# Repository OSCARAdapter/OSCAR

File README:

OSCAR
=====
A Retina screen controlling interface.

Getting Started
---------------
1) Clone this repository
2) make && make upload
3) There is no step 3

Licensing
---------
The software is licensed under the BSD 3-Clause License (check COPYING).
The hardware is licensed under CC-BY-SA.

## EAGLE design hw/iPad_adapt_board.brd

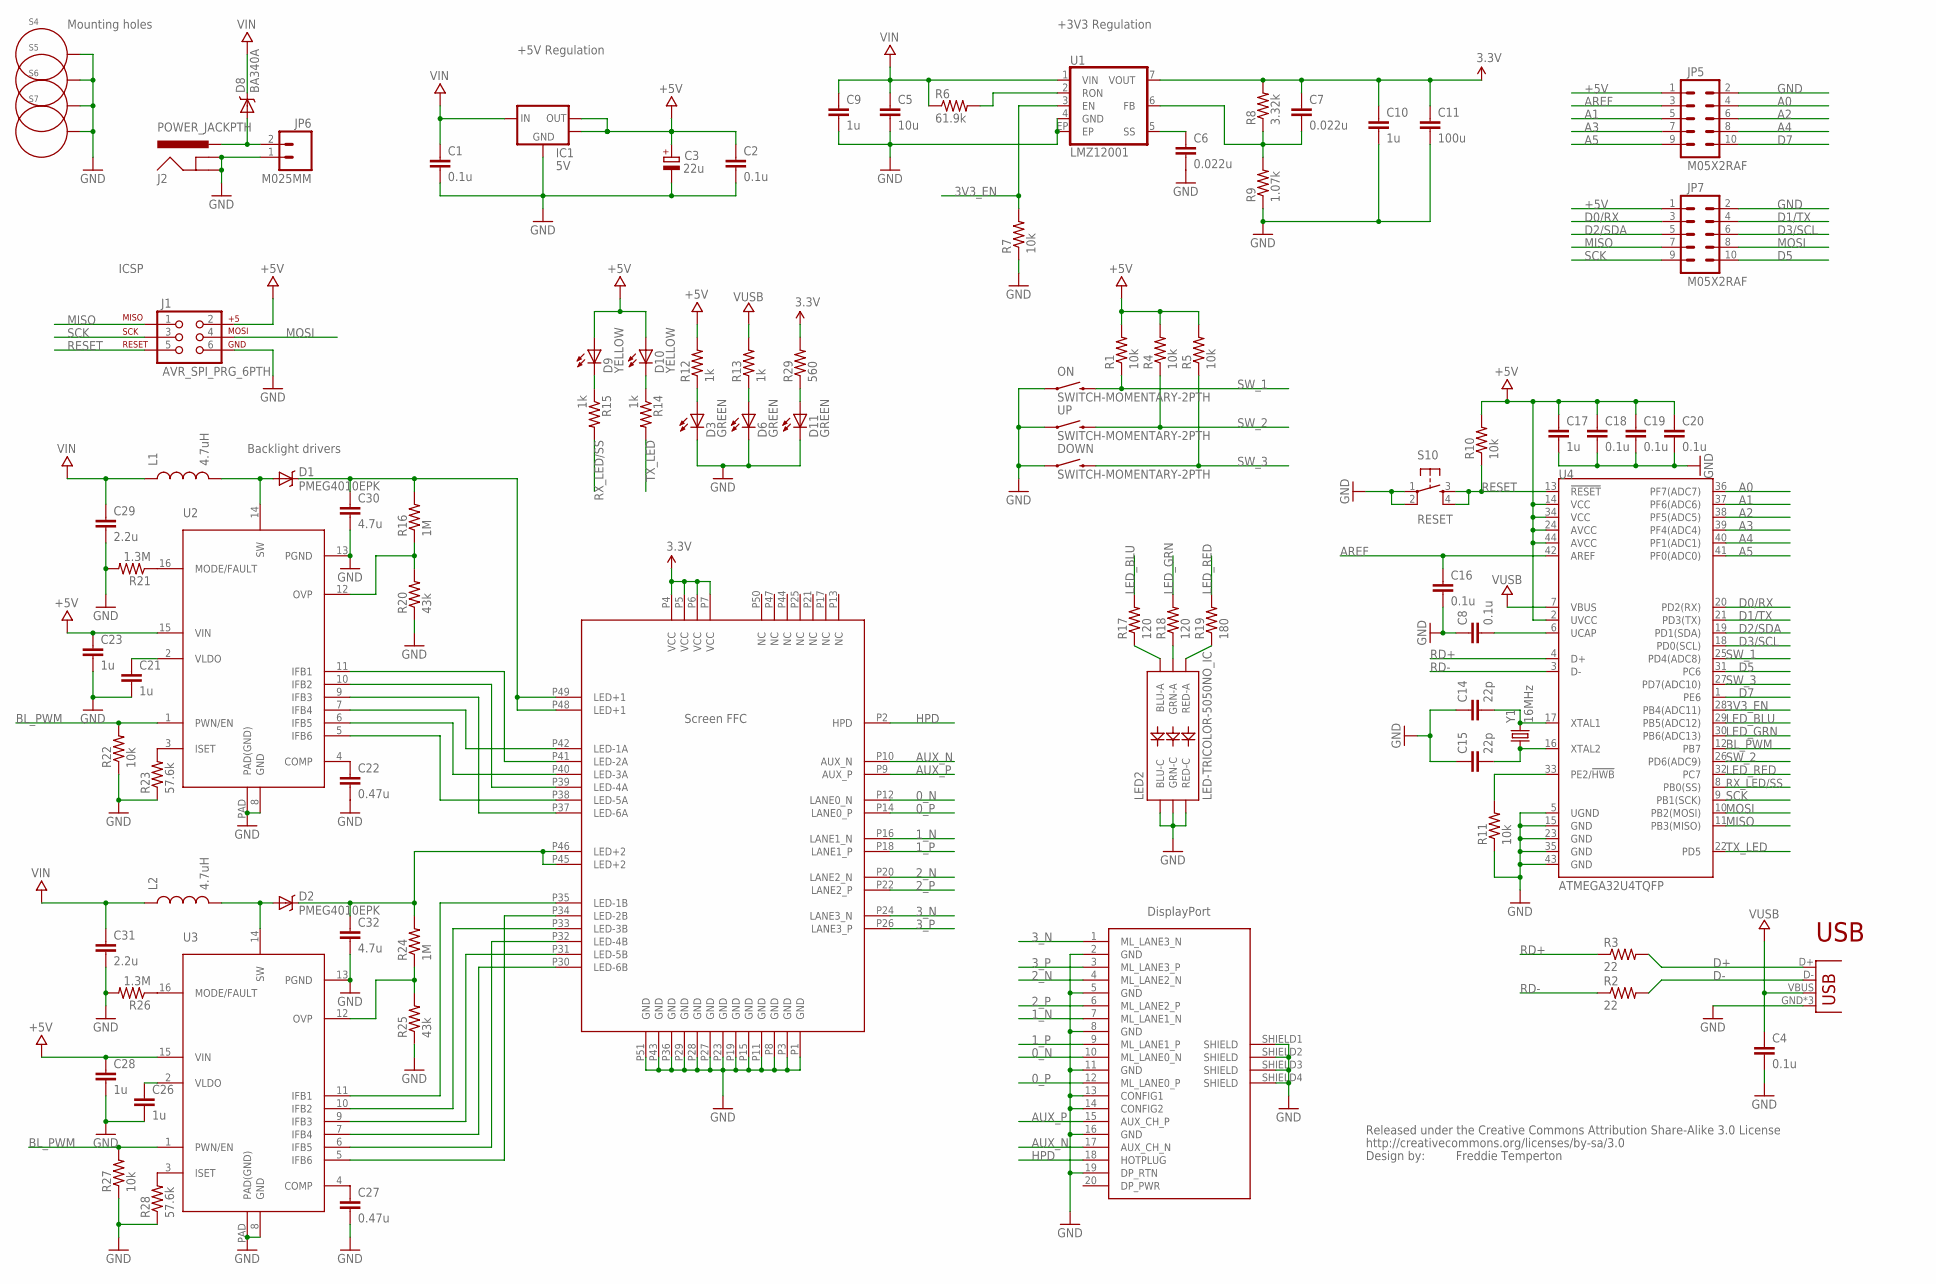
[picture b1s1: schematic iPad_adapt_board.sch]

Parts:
C1, C2, C4, C8, C16, C18, C19, C20: 0.1u; 0603-CAP
C3: 22u; SMC_B
C5: 10u; 1206
C6, C7: 0.022u; 0603-CAP
C9, C10: 1u; 1206
C11: 100u; C1210
C14, C15: 22p; 0603-CAP
C17, C21, C23, C26, C28: 1u; 0603-CAP
C22, C27: 0.47u; 0603-CAP
C29, C31: 2.2u; 0805
C30, C32: 4.7u; 0805
CC_TEXT1: CREATIVE_COMMONS
D1, D2: PMEG4010EPK; SOD1608
D3, D6, D11: GREEN; LED-0603
D8: BA340A; SMA-DIODE
D9, D10: YELLOW; LED-0603
DOWN: SWITCH-MOMENTARY-2PTH; TACTILE-PTH
IC1: 5V; SOT223
J1: AVR_SPI_PRG_6PTH; 2X3
J2: POWER_JACKPTH; POWER_JACK_PTH
J3: DP
J4: IPAD3-CONN; MOLEX502250-5191
JP1: USB-MICROB
JP5, JP7: M05X2RAF; 2X5-RAF
JP6: M025MM; SCREWTERMINAL-5MM-2
L1, L2: 4.7uH; SRN6045
LED2: LED-TRICOLOR-5050NO_IC; LED-TRICOLOR-5050
ON: SWITCH-MOMENTARY-2PTH; TACTILE-PTH
R1, R4, R5, R7, R10, R11, R22, R27: 10k; 0603-RES
R2, R3: 22; 0603-RES
R6: 61.9k; 0603-RES
R8: 3.32k; 0603-RES
R9: 1.07k; 0603-RES
R12, R13, R14, R15: 1k; 0603-RES
R16, R24: 1M; 0603-RES
R17, R18: 120; 0603-RES
R19: 180; 0603-RES
R20, R25: 43k; 0603-RES
R21, R26: 1.3M; 0603-RES
R23, R28: 57.6k; 0603-RES
R29: 560; 0603-RES
S4, S5, S6, S7: STANDOFF_ELECTRICAL; STANDOFF-ELECTRICAL
S10: RESET; TACTILE_SWITCH_SMD
U1: LMZ12001; TO-PMOD-7
U2, U3: TPS61176; QFN16
U4: ATMEGA32U4TQFP; SPARKFUN-DIGITALIC_TQFP44
UP: SWITCH-MOMENTARY-2PTH; TACTILE-PTH
Y1: 16MHz; CRYSTAL-TXC-7A

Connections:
0_N: J3.10 (ML_LANE0_N), J4.P12 (LANE0_N)
0_P: J3.12 (ML_LANE0_P), J4.P14 (LANE0_P)
1_N: J3.7 (ML_LANE1_N), J4.P16 (LANE1_N)
1_P: J3.9 (ML_LANE1_P), J4.P18 (LANE1_P)
2_N: J3.4 (ML_LANE2_N), J4.P20 (LANE2_N)
2_P: J3.6 (ML_LANE2_P), J4.P22 (LANE2_P)
3.3V: C7.1, C10.1, C11.1, J4.P4 (VCC), J4.P5 (VCC), J4.P6 (VCC), J4.P7 (VCC), R8.2, R29.2, U1.7 (VOUT)
3V3_EN: R7.2, U1.3 (EN), U4.28 (PB4(ADC11))
3_N: J3.1 (ML_LANE3_N), J4.P24 (LANE3_N)
3_P: J3.3 (ML_LANE3_P), J4.P26 (LANE3_P)
+5V: C2.1, C3.+, C17.1, C18.1, C19.1, C20.1, C23.1, C28.1, D9.A, D10.A, IC1.2 (OUT), IC1.4 (OUT), J1.2, JP5.1, JP7.1, R1.2, R4.2, R5.2, R10.2, R12.2, U2.15 (VIN), U3.15 (VIN), U4.2 (UVCC), U4.14 (VCC), U4.24 (AVCC), U4.34 (VCC), U4.44 (AVCC)
A0: JP5.4, U4.36 (PF7(ADC7))
A1: JP5.5, U4.37 (PF6(ADC6))
A2: JP5.6, U4.38 (PF5(ADC5))
A3: JP5.7, U4.39 (PF4(ADC4))
A4: JP5.8, U4.40 (PF1(ADC1))
A5: JP5.9, U4.41 (PF0(ADC0))
AREF: C16.1, JP5.3, U4.42 (AREF)
AUX_N: J3.17 (AUX_CH_N), J4.P10 (AUX_N)
AUX_P: J3.15 (AUX_CH_P), J4.P9 (AUX_P)
BL_PWM: R22.2, R27.2, U2.1 (PWN/EN), U3.1 (PWN/EN), U4.12 (PB7)
D0/RX: JP7.3, U4.20 (PD2(RX))
D1/TX: JP7.4, U4.21 (PD3(TX))
D2/SDA: JP7.5, U4.19 (PD1(SDA))
D3/SCL: JP7.6, U4.18 (PD0(SCL))
D5: JP7.10, U4.31 (PC6)
D7: JP5.10, U4.1 (PE6)
D+: JP1.D+, R3.2
D-: JP1.D-, R2.2
GND: C1.2, C2.2, C3.-, C4.2, C5.2, C6.2, C8.1, C9.2, C10.2, C11.2, C14.1, C15.1, C16.2, C17.2, C18.2, C19.2, C20.2, C21.2, C22.2, C23.2, C26.2, C27.2, C28.2, C29.2, C30.2, C31.2, C32.2, D3.C, D6.C, D11.C, DOWN.1, IC1.1 (ADJ), J1.6, J2.GND, J2.GNDBREAK, J3.2 (GND), J3.5 (GND), J3.8 (GND), J3.11 (GND), J3.13 (CONFIG1), J3.14 (CONFIG2), J3.16 (GND), J3.19 (DP_RTN), J3.SHIELD1 (SHIELD), J3.SHIELD2 (SHIELD), J3.SHIELD3 (SHIELD), J3.SHIELD4 (SHIELD), J4.P1 (GND), J4.P3 (GND), J4.P8 (GND), J4.P11 (GND), J4.P15 (GND), J4.P19 (GND), J4.P23 (GND), J4.P27 (GND), J4.P28 (GND), J4.P29 (GND), J4.P36 (GND), J4.P43 (GND), J4.P51 (GND), JP1.GND, JP1.MT1 (GND), JP1.MT2 (GND), JP5.2, JP6.1, JP7.2, LED2.4 (BLU-C), LED2.5 (RED-C), LED2.6 (GRN-C), ON.1, R7.1, R9.1, R11.1, R20.1, R21.2, R22.1, R23.1, R25.1, R26.2, R27.1, R28.1, S4.P1, S5.P1, S6.P1, S7.P1, S10.1, S10.2, U1.4 (GND), U1.EP, U2.8 (GND), U2.13 (PGND), U2.PAD (PAD(GND)), U3.8 (GND), U3.13 (PGND), U3.PAD (PAD(GND)), U4.5 (UGND), U4.15 (GND), U4.23 (GND), U4.35 (GND), U4.43 (GND), UP.1
HPD: J3.18 (HOTPLUG), J4.P2 (HPD)
LED_BLU: R17.2, U4.29 (PB5(ADC12))
LED_GRN: R18.2, U4.30 (PB6(ADC13))
LED_RED: R19.2, U4.32 (PC7)
MISO: J1.1, JP7.7, U4.11 (PB3(MISO))
MOSI: J1.4, JP7.8, U4.10 (PB2(MOSI))
unnamed: C6.1, U1.5 (SS)
unnamed: R6.2, U1.2 (RON)
unnamed: C7.2, R8.1, R9.2, U1.6 (FB)
unnamed: J4.P41 (LED-2A), U2.11 (IFB1)
unnamed: C8.2, U4.6 (UCAP)
unnamed: C14.2, U4.17 (XTAL1), Y1.P$2 (2)
unnamed: J4.P39 (LED-4A), U2.10 (IFB2)
unnamed: C15.2, U4.16 (XTAL2), Y1.P$1 (1)
unnamed: D3.A, R12.1
unnamed: D6.A, R13.1
unnamed: R11.2, U4.33 (PE2/!HWB)
unnamed: LED2.1 (GRN-A), R18.1
unnamed: D10.C, R14.1
unnamed: D9.C, R15.1
unnamed: R21.1, U2.16 (MODE/FAULT)
unnamed: LED2.3 (BLU-A), R17.1
unnamed: LED2.2 (RED-A), R19.1
unnamed: D1.A, L1.2, U2.14 (SW)
unnamed: C30.1, D1.C, J4.P48 (LED+1), J4.P49 (LED+1), R16.2
unnamed: R16.1, R20.2, U2.12 (OVP)
unnamed: J4.P37 (LED-6A), U2.9 (IFB3)
unnamed: C22.1, U2.4 (COMP)
unnamed: R23.2, U2.3 (ISET)
unnamed: J4.P42 (LED-1A), U2.7 (IFB4)
unnamed: C21.1, U2.2 (VLDO)
unnamed: J4.P40 (LED-3A), U2.6 (IFB5)
unnamed: J4.P38 (LED-5A), U2.5 (IFB6)
unnamed: R26.1, U3.16 (MODE/FAULT)
unnamed: D2.A, L2.2, U3.14 (SW)
unnamed: J4.P35 (LED-1B), U3.11 (IFB1)
unnamed: R24.1, R25.2, U3.12 (OVP)
unnamed: C27.1, U3.4 (COMP)
unnamed: R28.2, U3.3 (ISET)
unnamed: C26.1, U3.2 (VLDO)
unnamed: J4.P33 (LED-3B), U3.10 (IFB2)
unnamed: J4.P31 (LED-5B), U3.9 (IFB3)
unnamed: J4.P32 (LED-4B), U3.6 (IFB5)
unnamed: J4.P34 (LED-2B), U3.5 (IFB6)
unnamed: D11.A, R29.1
unnamed: C32.1, D2.C, J4.P45 (LED+2), J4.P46 (LED+2), R24.2
unnamed: D8.A, J2.PWR, JP6.2
unnamed: J4.P30 (LED-6B), U3.7 (IFB4)
RD+: R3.1, U4.4 (D+)
RD-: R2.1, U4.3 (D-)
RESET: J1.5, R10.1, S10.3, S10.4, U4.13 (!RESET)
RX_LED/SS: R15.2, U4.8 (PB0(SS))
SCK: J1.3, JP7.9, U4.9 (PB1(SCK))
SW_1: ON.3 (2), R1.1, U4.25 (PD4(ADC8))
SW_2: R4.1, U4.26 (PD6(ADC9)), UP.3 (2)
SW_3: DOWN.3 (2), R5.1, U4.27 (PD7(ADC10))
TX_LED: R14.2, U4.22 (PD5)
VIN: C1.1, C5.1, C9.1, C29.1, C31.1, D8.C, IC1.3 (IN), L1.1, L2.1, R6.1, U1.1 (VIN)
VUSB: C4.1, JP1.VBUS, R13.2, U4.7 (VBUS)

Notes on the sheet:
USB
Freddie Temperton
Screen FFC
DisplayPort
Mounting holes
+5V Regulation
+3V3 Regulation
ICSP
Backlight drivers

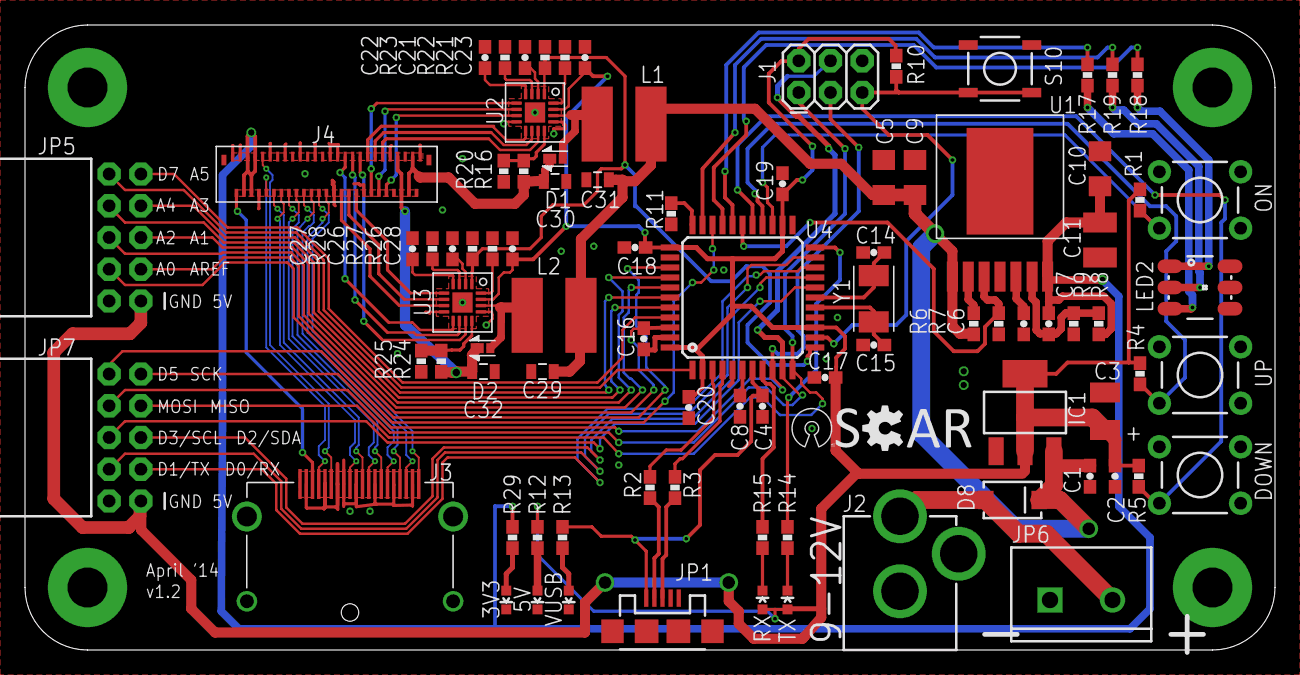
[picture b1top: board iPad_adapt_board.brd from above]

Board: 2 copper layers, 100.0 x 50.0 mm, 91 parts (0 on the bottom side), 89 nets.

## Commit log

2014-02-08 Add raw arduino + makefile repos
2014-02-09 Add old arduino code
2014-02-09 Base commit for the new firmware
2014-02-09 Add readme/copying
2014-02-09 Implement backlight up/down
2014-02-09 Let backlight restore last recorded level
2014-02-09 Add switch pin definitions, fix pin for backlight
2014-02-09 Enable backlight power supply on/off
2014-02-09 Add support for the 3 switches
2014-02-09 Fix assorted compilation issues
2014-02-09 Add makefile for use with Arduino-Makefile
2014-02-09 Add gitignore
2014-02-09 Add initial ui mockup
2014-02-09 Add base software code and build system
2014-02-09 Modify gitignore for software
2014-02-09 Fix some issues with firmware when tested on actual hardware
2014-02-09 Fix PWM not changing
2014-02-09 Add buttons and bodges to mainwindow
2014-02-09 Add todo for slider changed
2014-02-09 Don't allow swo to commit
2014-02-09 Fix for qt5 syntax
2014-02-09 Remove old firmware, move new to top-level
2014-02-09 Fix board type and use custom core
2014-02-09 Rebuild UI in a better way
2014-02-09 Tweak UI to use less vertical space
2014-02-09 Add WinExtras to project for windows builds
2014-02-09 If composition is possible, make bg full glass
    Untested!
2014-02-10 Enable NoSystemBackground for full glass!
2014-02-10 Add OSCAR logos
2014-02-10 Add OSCAR icons to ui
2014-02-10 Shrink ui a bit
2014-02-12 Declare all supported USB commands
2014-02-12 Add read-back support for RGB led
2014-02-12 Add usb command handling to AdapterBoard
2014-02-12 Document the usb protocol (ish)
2014-02-12 Add usb_commands.h to SW/ as a symlink
2014-02-12 Convert mainwindow to a QWidget
2014-02-12 Tweak stylizing...
2014-02-12 Create a thread to handle device interaction in
    You would never do it in the UI thread (right?)
2014-02-12 Create a board-specific libusb'ing class
    Defines:
    - find the device
    - send a command (and get ack)
    - nothing else...
2014-02-12 Fix some whitespace in mainwindow.h
2014-02-12 Define sendCmd overloads in useful size
2014-02-12 Add convience methods for backlight operations
2014-02-12 Add all these new files to the Qmake project
2014-02-14 Remove convenience methods, add isConnected()
2014-02-16 Start device thread in mainwindow
2014-02-16 Add a macro to determine whether a GET command
2014-02-16 Define the devicethread
2014-02-16 Let sendCmd support 'GET's
2014-02-16 Add 3-arg3 read alias of sendCmd
2014-02-16 Handle get command response parsin
2014-02-16 Connect device connected/disconnected states
2014-02-16 Fix assorted syntax errors
2014-02-16 Link to libusb1.0
2014-02-16 Implement undecelared functions
2014-02-17 Use sleep and emit
2014-02-17 Use public slots declarations
2014-02-17 Define setBacklightPower/setBacklightLevel
2014-02-17 Make deviceConnected/disconnected useful
2014-02-17 Add statusLabel
2014-02-18 Use valueChanged not sliderMoved
2014-02-18 Use sleep/msleep correctly
2014-02-18 memcpy to the correct place
2014-02-18 Remove bodge code
2014-02-18 Force backlight type to be uint8_t
2014-02-18 Reduce sleep time between commands
2014-02-18 Change disconnected message
2014-02-18 Compress up again
2014-02-18 Add libusbx 64bit to project file
2014-02-20 Fix the background rendering glitch under windows
2014-04-05 Bump Arduino subproject to include OSCAR variant
2014-04-05 Update gitignore to hide VS build directories
2014-04-05 Hide generated VS solution from Qt
2014-04-05 Add template nsis script and license
2014-05-24 Change Arduino submodule to refer to the OSCAR variant
2014-05-24 Add required windows DLLs for Qt5 and libusb to installer/
2014-05-24 Add generated installer to gitignore
2014-05-24 Replace with a new readme.
    Extend using markdown to include full build information and a repository
    overview.
2014-05-24 Add hardware
2014-05-24 Update submodule urls
2014-06-19 Prepare for release by building 32bit and test drivers
2014-07-02 Implement backlight and panel delays as given
    The datasheet for the LP097QX1-SPA1-8M1 states that the power must be
    provided prior to the backlight being enabled, and that the backlight
    must be disabled prior to the panel.
2014-07-03 Add latest case designs to hw/
2014-07-12 Set the LED on prior to the power to the display
    This provides a more 'responsive' UI for the user
2014-07-12 Change debouncing to use Bounce2 library
2014-07-12 Increase debounce delay notably
2014-07-12 Fix: LED was not changed when toggled via USB
2014-07-12 Revert "Change debouncing to use Bounce2 library"
    This reverts commit 79a57e29385afc175ce4598ae7b8515164baa9c4.
    Conflicts:
    fw/libs/AdapterBoard/AdapterBoard.cpp
2014-07-12 Increase magic delay number by 2 roders of magnitude
2014-07-12 Increase button delay by 5x
2014-07-12 Set LED off before backlight
2014-07-13 Change to use millis() to ensure minimum time between switch polls
2014-07-13 Revert "Change to use millis() to ensure minimum time between switch polls"
    This reverts commit 62b84387c85cd28378d28a473ed3bb4aa6b99e1e.
2014-07-13 Improve button debouncing using 2 history tracking
2014-07-13 Use a third colour of on and using USB
2014-07-13 Swap Red and Green channels for the actual part
2014-07-13 Reduce LED power
2014-07-13 Latch power state for 300ms
2014-07-13 Force backlight off during initialization, keep state during soft cycle
2014-07-13 Only care about up/down switches if backlight is on
2014-07-13 Save and restore previous backlight state during soft cycle
2014-07-13 Only allow backlight changes every 300ms
2014-07-13 If backlight 'remembered' value is 0, set to max
2014-07-13 Flatten nested backlight if
2014-07-13 Revert "Only allow backlight changes every 300ms"
    This reverts commit eaef4d01b27e5d0a3754995063d2b0f72aae427c.
    Conflicts:
    fw/libs/AdapterBoard/AdapterBoard.cpp
2014-07-13 Don't do anything if up/down are called whilst off
2014-07-13 Try to 'latch' up/down buttons
2014-07-13 Ignore USB backlight set packet if display off
2014-07-13 Create set function which doesn't actually output, but updates the state
2014-07-13 Force switch polling to be at ~10ms intervals
2014-07-13 Revert "Force switch polling to be at ~10ms intervals"
    This reverts commit 5a4b9d49a8a98e4f83066dce59978ee33e38d56a.
2014-07-13 Revert "Try to 'latch' up/down buttons"
    This reverts commit 57e47e9f0008d73847a03f2e7c2a885c4ec899db.
2014-07-13 Backlight.set updates the eeprom, and changes backlight only if the display is on
2014-07-14 Revert "Revert "Change debouncing to use Bounce2 library""
    This reverts commit 1fdc3cb12a39859c43eed1679d2ae6670f4d882b.
    Conflicts:
    fw/libs/AdapterBoard/AdapterBoard.cpp
    fw/libs/AdapterBoard/AdapterBoard.h
    This implements the bounce library correctly...
2014-10-12 Production OSCAR board files
2014-10-12 Revert "Production OSCAR board files"
    This reverts commit 5a923e2bebfcaec13dcdf26a45b099b8b35ddb17.
2014-10-12 Case files in dxf added
2014-10-18 Restore last backlight power state when booted
2014-10-23 Update comment, init switches then backlight works, add else
2019-10-29 Editing README.md file

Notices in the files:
parts and their libraries:
SparkFun-Connectors: Licensing: CC v3.0 Share-Alike You are welcome to use this library for commercial purposes.
SparkFun-Aesthetics: Released under the Creative Commons Attribution Share-Alike 3.0 License
SparkFun-Aesthetics: http://creativecommons.org/licenses/by-sa/3.0
